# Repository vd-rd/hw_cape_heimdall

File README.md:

# hw_cape_heimdall
Motion detection hardware cape via multiple technologies (PiR - Passive Infrared, ToF - Time of Flight, FiR - Far infrared)

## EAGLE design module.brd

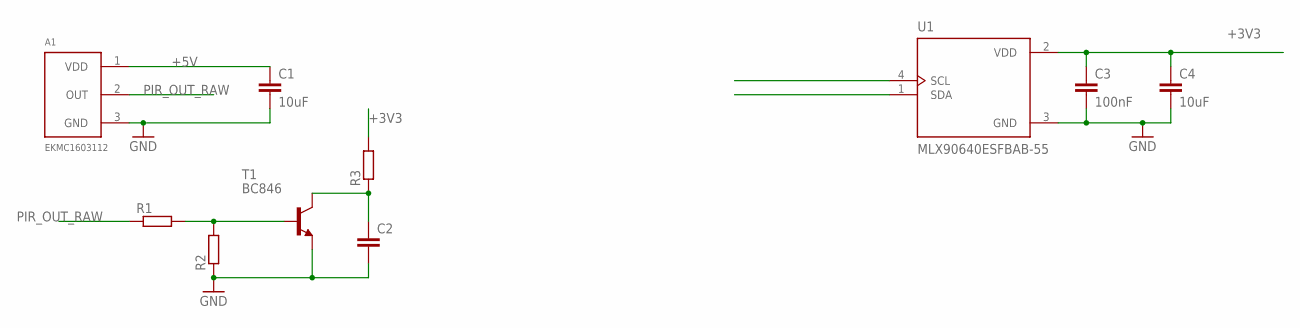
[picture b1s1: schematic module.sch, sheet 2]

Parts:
A1: EKMC1603112; TO254P2200H2020-3
C1, C4: 10uF; C0805
C2: C-EUC0603; C0603
C3: 100nF; C0603
R1, R2, R3: R-EU_R0603; R0603
T1: BC846; SOT23
U1: MLX90640ESFBAB-55; TO292-55

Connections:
+3V3: C3.1, C4.1, R3.2, U1.2 (VDD)
+5V: A1.1 (VDD), C1.1
GND: A1.3 (GND), C1.2, C2.2, C3.2, C4.2, R2.1, T1.2 (E), U1.3 (GND)
unnamed: R1.2, R2.2, T1.1 (B)
unnamed: C2.1, R3.1, T1.3 (C)
PIR_OUT_RAW: A1.2 (OUT), R1.1

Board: 2 copper layers, 10 parts (0 on the bottom side), 6 nets, no tracks yet.

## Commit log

2020-01-17 project: added pir and fir
2020-01-17 project: initial floorplaning for board
